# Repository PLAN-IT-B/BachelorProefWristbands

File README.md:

# BachelorProefWristbands
Finalcode repo voor Jonas Piscador en Robin Missiaen

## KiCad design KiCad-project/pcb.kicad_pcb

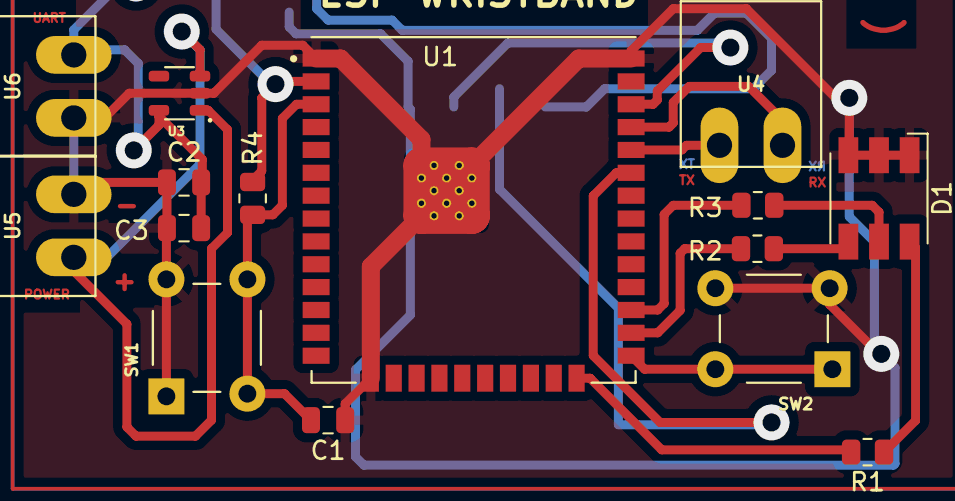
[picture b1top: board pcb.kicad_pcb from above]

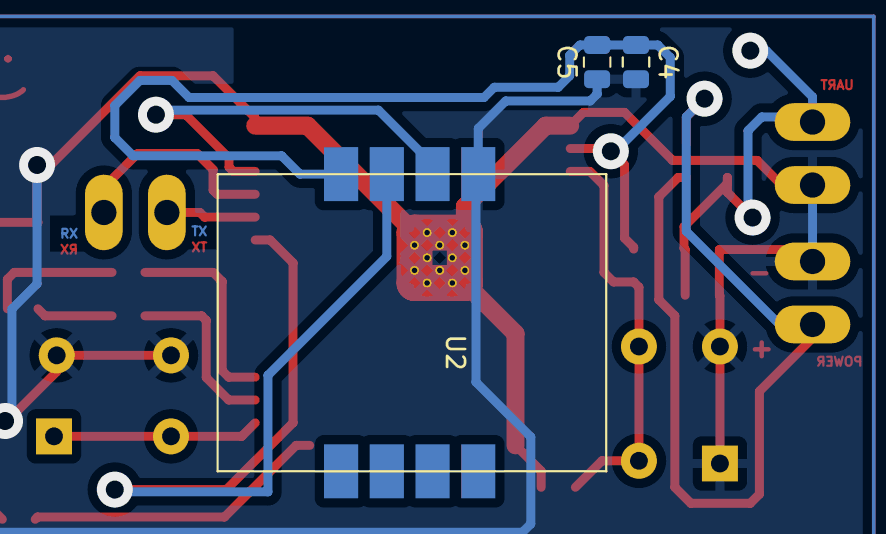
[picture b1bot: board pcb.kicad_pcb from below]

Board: 2 copper layers, 18 parts (3 on the bottom side), 15 nets.

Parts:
C1: 1u; C_0805_2012Metric
C2: 22u; C_0805_2012Metric
C3: 100n; C_0805_2012Metric
C4, C5: 10u; C_0805_2012Metric
D1: LED_RGB; LED_RGB_5050-6
R1, R2, R3: 68; R_0805_2012Metric
R4: 10k; R_0805_2012Metric
SW1: EN; TE_3-1825910-1
SW2: BOOT; TE_3-1825910-1
U1: ESP32-WROOM-32UE(M113EH6400UH3Q0); MODULE_ESP32-WROOM-32UE(M113EH6400UH3Q0)
U2: MAX30102; Hartsensor
U3: MIC5504-2.5YM5-T5; SOT23-5P95_280X145XL45X37N
U4, U5, U6: 15EDGRC-3.5-2P; 15EDGRC-3.5-2P-PAK

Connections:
GND: C1.1, C2.1, C3.1, C4.1, C5.1, D1.1 (RK), D1.2 (GK), D1.3 (BK), SW1.1, SW1.2, SW2.3, SW2.4, U1.1 (GND), U1.15 (GND), U1.38 (GND), U1.39_1 (GND), U1.39_2 (GND), U1.39_3 (GND), U1.39_4 (GND), U1.39_5 (GND), U1.39_6 (GND), U1.39_7 (GND), U1.39_8 (GND), U1.39_9 (GND), U1.39_10 (GND), U1.39_11 (GND), U1.39_12 (GND), U1.39_13 (GND), U1.39_14 (GND), U1.39_15 (GND), U1.39_16 (GND), U1.39_17 (GND), U1.39_18 (GND), U1.39_19 (GND), U1.39_20 (GND), U1.39_21 (GND), U2.8 (GND), U3.2 (GND), U5.P$2, U6.P$1
unnamed: C1.2, R4.1, SW1.3, SW1.4, U1.3 (EN)
unnamed: C2.2, C3.2, C4.2, C5.2, R4.2, U1.2 (3V3), U2.5 (VIN), U3.5 (VOUT), U6.P$2
unnamed: D1.4 (BA), R2.1
unnamed: D1.5 (GA), R3.1
unnamed: D1.6 (RA), R1.1
unnamed: R1.2, U1.24 (IO2)
unnamed: R2.2, U1.26 (IO4)
unnamed: R3.2, U1.27 (IO16)
unnamed: SW2.1, SW2.2, U1.25 (IO0)
unnamed: U1.33 (IO21), U2.6 (SDA)
unnamed: U1.34 (RXD0), U4.P$1
unnamed: U1.35 (TXD0), U4.P$2
unnamed: U1.36 (IO22), U2.7 (SCL)
unnamed: U3.1 (VIN), U3.3 (EN), U5.P$1

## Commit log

2022-02-22 BlokSchema+GanttChart
2022-03-08 blablabla
2022-03-08 rssi
2022-03-08 ECHTE CODE voor 4 aespas
2022-03-08 ready 4esps
2022-03-08 update main
2022-03-08 update espoas
2022-03-08 Update Main 8 maart
2022-04-12 ffds
2022-05-13 kicad
2022-05-23 fotos
2022-05-23 veranderen tip
